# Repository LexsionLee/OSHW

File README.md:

# Lexsion 设计的开源硬件

> Open-source Hardware design from Lexsion

## 简介：

仓库名称取OSHW，顾名思义，本仓库存储 Lexsion 的开源硬件项目。因为贫穷导致无力购买高性能的新电脑以运行卡顿的Altium Designer ，外加近段时间其名声不好，笔者打算换一款EDA工具。听闻KiCad是一款开源的设计工具，于是笔者就选择了它。考虑开源硬件的特殊性，使用商业的EDA工具设计可能并不是一个好的选择，因此本项目下所有PCB设计，都是使用KiCad完成的。

每个项目相关内容存储在以项目名称命名的单独目录中。

### 项目目录内应该包含以下内容：

* Schematic design （KiCad 5.1x or KiCad 6(Future) ）
* PCB design （KiCad 5.1x or KiCad 6(Future) ）
* 自建 符号库 与 封装库 （KiCad 5.1x or KiCad 6(Future) ）
* PDF 打印的 Schematic （方便使用PDF Reader直接阅读）
* GERBER （方便直接发送给PCB制造商以进行制造）
* README.md （介绍项目内容、相关事项）

## 注意：

笔者本仓库下发布这些硬件设计的目的旨在研究和分享。这些设计视其所处的阶段可能没有被实际生产或大量测试过，因笔者技术水平所限，无法保证它们在实际使用中是否可以正常工作。因此 Lexsion 不对使用这些文件产生的损失或风险承担任何责任。这里不提供任何保障！(It's absolutely no WARRANTY.)

本仓库下的相关硬件设计有参考其他设计，笔者会避免将明确声明了禁止参考的内容应用于此处设计。如果此处的某些设计对您或您所在的组织构成侵权，您可以与我取得联系。

i[AT]lexsion.net，将[AT]换成@可邮件联系我。

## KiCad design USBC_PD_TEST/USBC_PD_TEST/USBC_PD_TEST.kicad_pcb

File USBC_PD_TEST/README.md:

# USBC_PD_TEST

此项目是一个用于USBC口下快速充电协议分析测试的转接板，采用四层板结构，确保能通过大电流。电源部分宽走线与接线柱设计，应该能轻易通过5A电流，测试环便于挂接逻辑分析仪。笔者主要用于学习PD规范过程中的实验验证，限于笔者才疏学浅，该测试板可能会有BUG，有问题欢迎反馈。

**注意：此项目暂未实际测试。**

## 效果图：

### 2D：

### 3D：

## 基本信息：

| 项目名称  | USBC_PD_TEST     |
| --------- | ---------------- |
| PCB工艺   | 0.8mm四层玻纤板  |
| PCB数量   | 1                |
| PCB尺寸   | 约49.5 * 40 (mm) |
| KiCad版本 | 6.0.4            |

## 其他事项：

该板要安装Type-C公头，板厚必须为0.8mm!

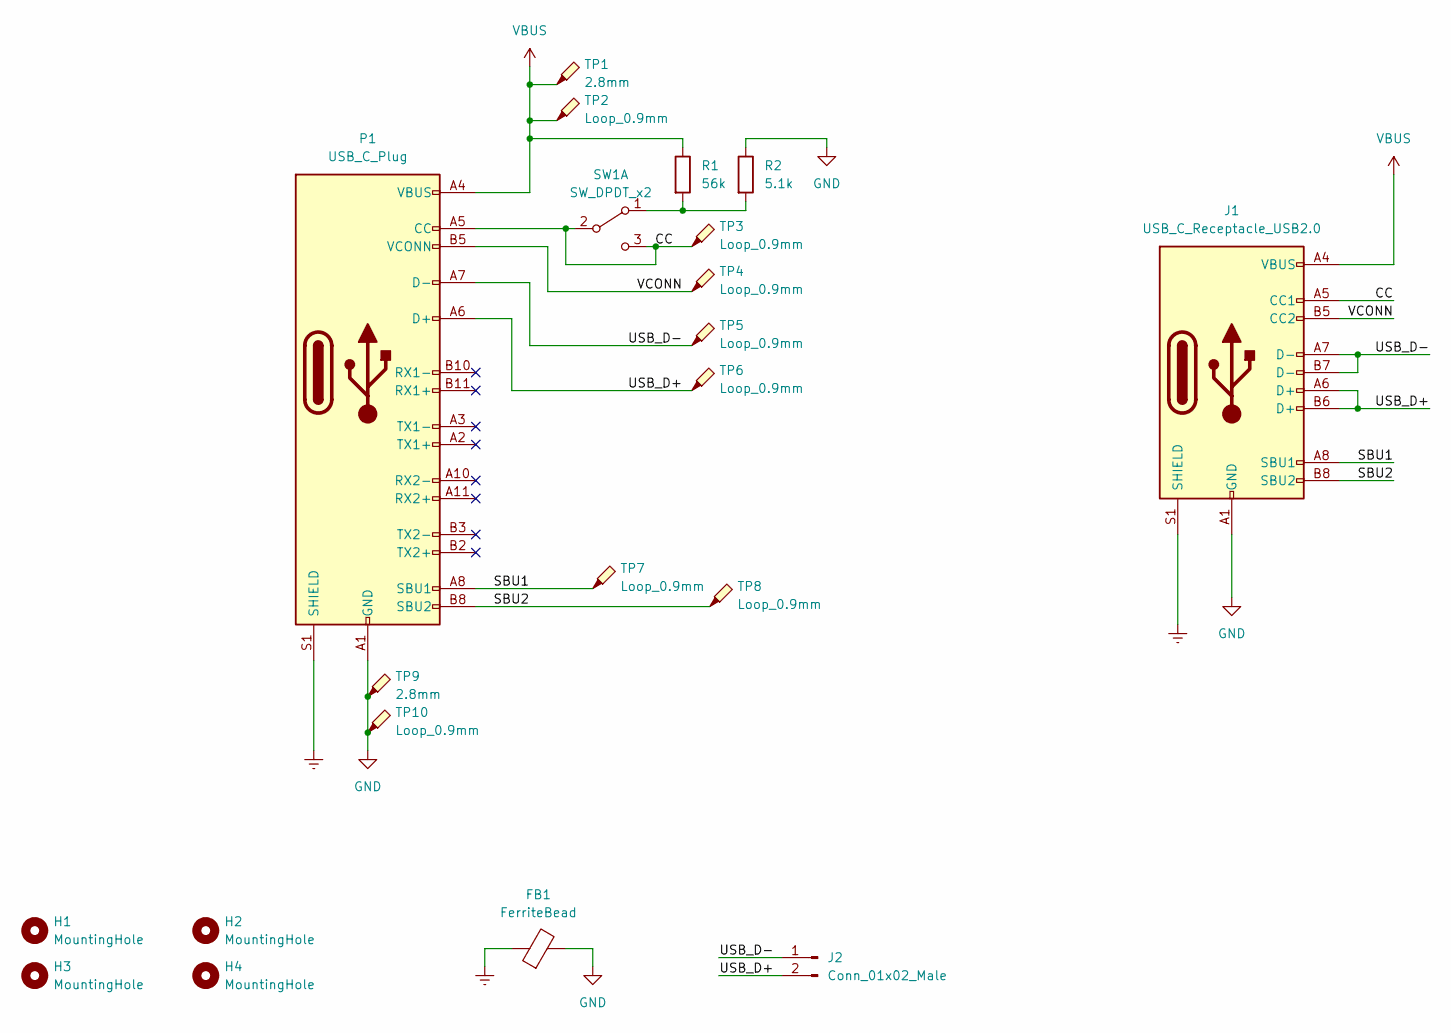
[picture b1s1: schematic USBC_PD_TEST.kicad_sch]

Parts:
FB1: FerriteBead; L_0603_1608Metric
H1, H2, H3, H4: MountingHole; MountingHole_3.2mm_M3_Pad_Via
J1: USB_C_Receptacle_USB2.0; USB_C_Receptacle_Palconn_UTC16-G
J2: Conn_01x02_Male; PinHeader_1x02_P2.54mm_Vertical
P1: USB_C_Plug; USB_C_Plug_Molex_105444
R1: 56k; R_0402_1005Metric
R2: 5.1k; R_0402_1005Metric
SW1: SW_DPDT_x2; SW_DPDT_MSS22D18
TP1, TP9: 2.8mm; TestPoint_Loop_D3.80mm_Drill2.8mm
TP2, TP3, TP4, TP5, TP6, TP7, TP8, TP10: Loop_0.9mm; TestPoint_Loop_D2.60mm_Drill0.9mm_Beaded

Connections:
/CC: J1.A5 (CC1), P1.A5 (CC), SW1.2 (B), SW1.3 (C), TP3.1
/SBU1: J1.A8 (SBU1), P1.A8 (SBU1), TP7.1
/SBU2: J1.B8 (SBU2), P1.B8 (SBU2), TP8.1
/USB_D+: J1.A6 (D+), J1.B6 (D+), J2.2, P1.A6 (D+), TP6.1
/USB_D-: J1.A7 (D-), J1.B7 (D-), J2.1, P1.A7 (D-), TP5.1
/VCONN: J1.B5 (CC2), P1.B5 (VCONN), TP4.1
Earth: FB1.1, J1.S1 (SHIELD), P1.S1 (SHIELD)
GND: FB1.2, J1.A1 (GND), J1.A12 (GND), J1.B1 (GND), J1.B12 (GND), P1.A1 (GND), P1.A12 (GND), P1.B1 (GND), P1.B12 (GND), R2.1, TP9.1, TP10.1
unnamed: R1.2, R2.2, SW1.1 (A)
VBUS: J1.A4 (VBUS), J1.A9 (VBUS), J1.B4 (VBUS), J1.B9 (VBUS), P1.A4 (VBUS), P1.A9 (VBUS), P1.B4 (VBUS), P1.B9 (VBUS), R1.1, TP1.1, TP2.1

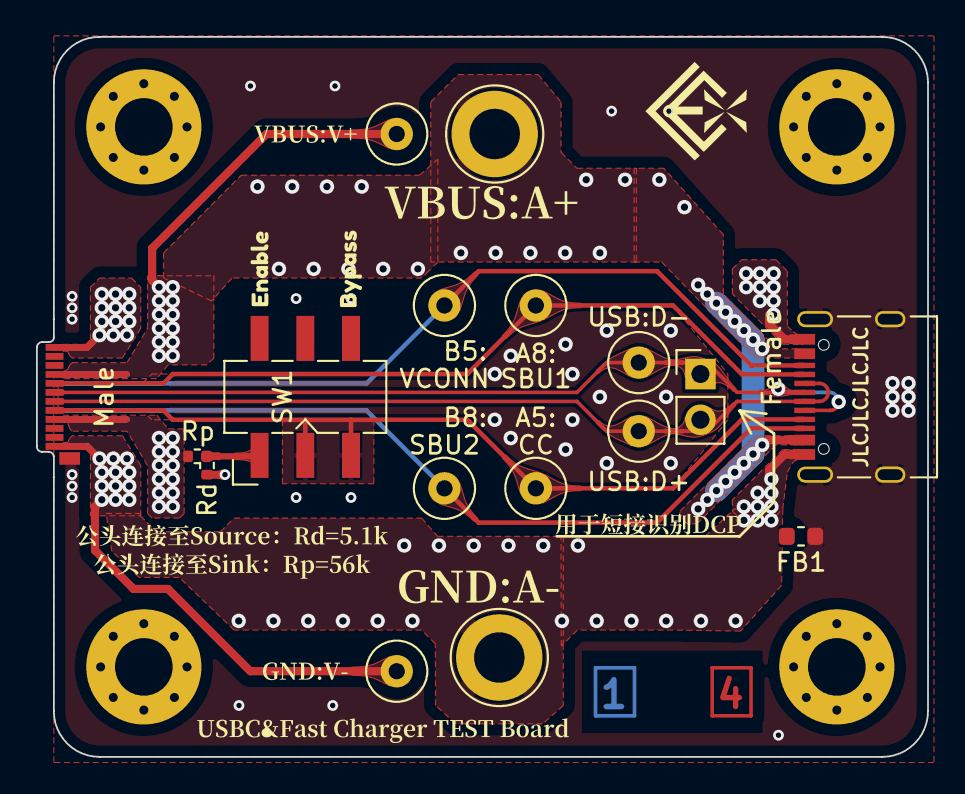
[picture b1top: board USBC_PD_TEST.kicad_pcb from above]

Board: 4 copper layers, 49.5 x 40.0 mm, 32 parts (1 on the bottom side), 10 nets.

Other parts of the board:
kibuzzard-6262F4E3: G***; kibuzzard-6262F4E3
kibuzzard-6262F4EB: G***; kibuzzard-6262F4EB
kibuzzard-6262F531: G***; kibuzzard-6262F531
kibuzzard-6262F952: G***; kibuzzard-6262F952
kibuzzard-6262FE0A: G***; kibuzzard-6262FE0A
kibuzzard-6262FE8D: G***; kibuzzard-6262FE8D
kibuzzard-6263C95A: G***; kibuzzard-6263C95A
kibuzzard-6263F752: G***; kibuzzard-6263F752
kibuzzard-62641BEE: G***; kibuzzard-62641BEE
kibuzzard-62641C40: G***; kibuzzard-62641C40
kibuzzard-62641778: G***; kibuzzard-62641778

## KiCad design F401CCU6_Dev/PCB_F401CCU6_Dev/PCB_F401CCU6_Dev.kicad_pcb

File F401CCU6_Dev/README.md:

# F401CCU6_Dev

此项目的目标是做一个引出所有IO，以实现一个F401CCU6开发板的效果。参考了网上常见的板型，加入了RGB灯。

该项目MCU采用的STM32F1401CCU6，偶然翻出几年前留下的几枚mPOS也是画这板子的原因之一。该板设计了RST、BOOT按键，并引出了SWD调试接口，同时为了迎合时代发展，USB采用了Type C接口。

## 效果图：

**实物图：**

**2D：**

**3D：**

## 基本信息：

| 项目名称  | F401CCU6_Dev   |
| --------- | -------------- |
| PCB工艺   | 双面玻纤板     |
| PCB数量   | 1              |
| PCB尺寸   | 约57 * 23 (mm) |
| KiCad版本 | 6.0.4          |

## 其他事项：

暂无。

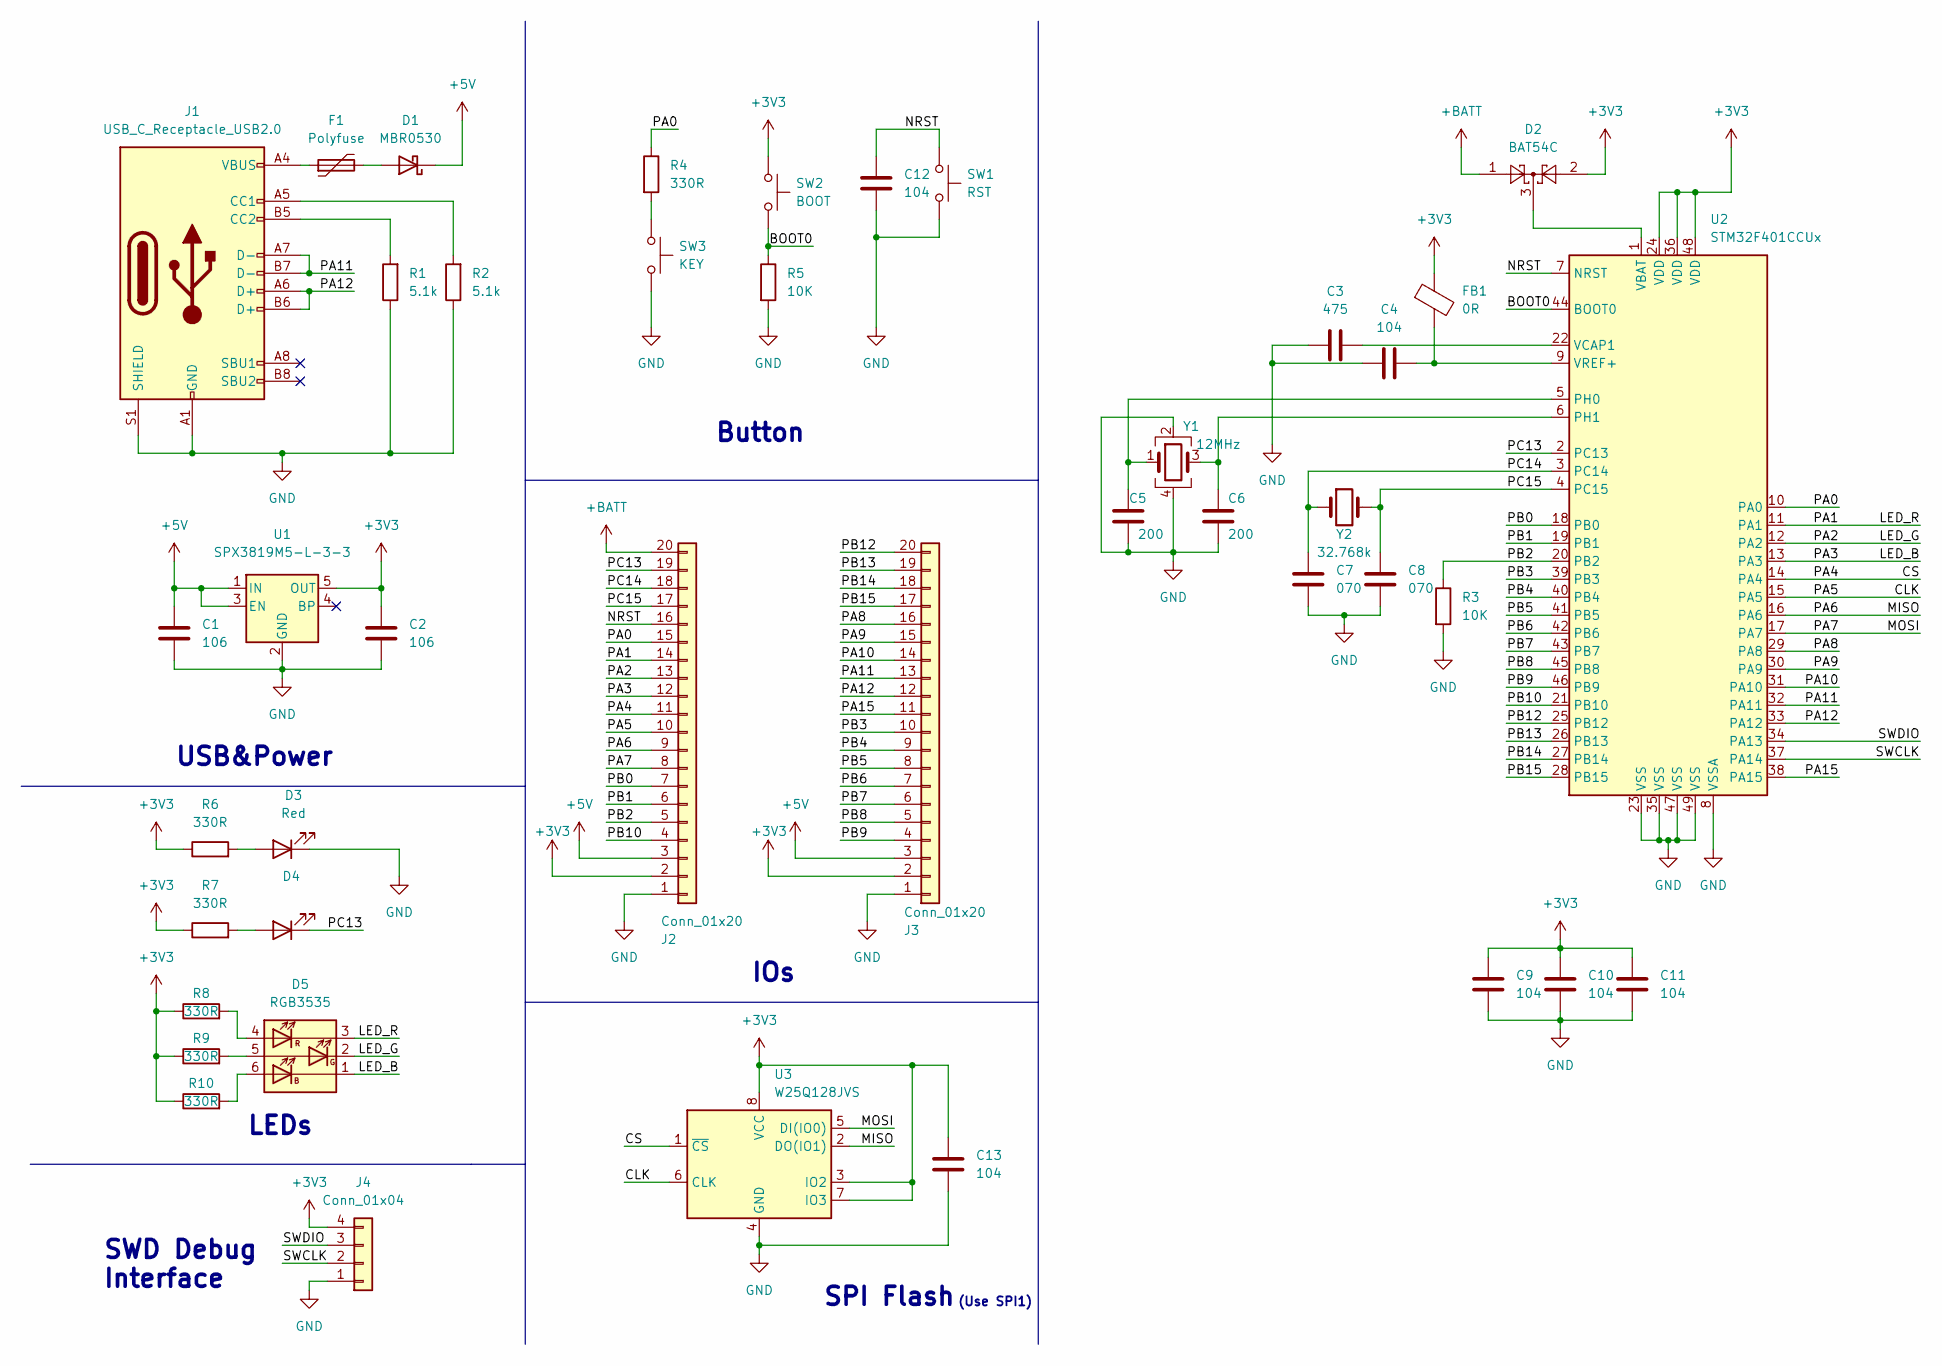
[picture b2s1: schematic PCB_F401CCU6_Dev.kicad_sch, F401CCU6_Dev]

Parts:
C1, C2: 106; C_0603_1608Metric
C3: 475; C_0402_1005Metric
C4, C9, C10, C11, C12, C13: 104; C_0402_1005Metric
C5, C6: 200; C_0402_1005Metric
C7, C8: 070; C_0402_1005Metric
D1: MBR0530; D_SOD-123
D2: BAT54C; SOT-23
D3: Red; LED_0603_1608Metric
D4: (no value)
D5: RGB3535; LED_RGB_3535
F1: Polyfuse; Fuse_0603_1608Metric
FB1: 0R; L_0603_1608Metric
J1: USB_C_Receptacle_USB2.0; USB_C_Receptacle_Palconn_UTC16-G
J2, J3: Conn_01x20; PinHeader_1x20_P2.54mm_Vertical
J4: Conn_01x04; PinHeader_1x04_P2.54mm_Horizontal
R1, R2: 5.1k; R_0402_1005Metric
R3, R5: 10K; R_0402_1005Metric
R4, R6, R7, R8, R9, R10: 330R; R_0402_1005Metric
SW1: RST; SW_Push_1P1T_TC026X
SW2: BOOT; SW_Push_1P1T_TC026X
SW3: KEY; SW_Push_1P1T_TC048X
U1: SPX3819M5-L-3-3; SOT-23-5
U2: STM32F401CCUx; QFN-48-1EP_7x7mm_P0.5mm_EP5.6x5.6mm
U3: W25Q128JVS; SOIC-8_5.23x5.23mm_P1.27mm
Y1: 12MHz; Crystal_SMD_3225-4Pin_3.2x2.5mm
Y2: 32.768k; Crystal_SMD_3215-2Pin_3.2x1.5mm

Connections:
+3V3: C2.1, C9.1, C10.1, C11.1, C13.1, D2.2, FB1.1, J2.2, J3.2, J4.4, R6.1, R7.1, R8.1, R9.1, R10.1, SW2.1, U1.5 (OUT), U2.24 (VDD), U2.36 (VDD), U2.48 (VDD), U3.3 (IO2), U3.7 (IO3), U3.8 (VCC)
+5V: C1.1, D1.1 (K), J2.3, J3.3, U1.1 (IN), U1.3 (EN)
+BATT: D2.1, J2.20
/BOOT0: R5.1, SW2.2, U2.44 (BOOT0)
/CLK: J2.10, U2.15 (PA5), U3.6 (CLK)
/CS: J2.11, U2.14 (PA4), U3.1 (~CS)
/LED_B: D5.1 (KB), J2.12, U2.13 (PA3)
/LED_G: D5.2 (KG), J2.13, U2.12 (PA2)
/LED_R: D5.3 (KR), J2.14, U2.11 (PA1)
/MISO: J2.9, U2.16 (PA6), U3.2 (DO(IO1))
/MOSI: J2.8, U2.17 (PA7), U3.5 (DI(IO0))
/NRST: C12.1, J2.16, SW1.1, U2.7 (NRST)
/PA0: J2.15, R4.1, U2.10 (PA0)
/PA8: J3.16, U2.29 (PA8)
/PA9: J3.15, U2.30 (PA9)
/PA10: J3.14, U2.31 (PA10)
/PA11: J1.A7 (D-), J1.B7 (D-), J3.13, U2.32 (PA11)
/PA12: J1.A6 (D+), J1.B6 (D+), J3.12, U2.33 (PA12)
/PA15: J3.11, U2.38 (PA15)
/PB0: J2.7, U2.18 (PB0)
/PB1: J2.6, U2.19 (PB1)
/PB2: J2.5, R3.1, U2.20 (PB2)
/PB3: J3.10, U2.39 (PB3)
/PB4: J3.9, U2.40 (PB4)
/PB5: J3.8, U2.41 (PB5)
/PB6: J3.7, U2.42 (PB6)
/PB7: J3.6, U2.43 (PB7)
/PB8: J3.5, U2.45 (PB8)
/PB9: J3.4, U2.46 (PB9)
/PB10: J2.4, U2.21 (PB10)
/PB12: J3.20, U2.25 (PB12)
/PB13: J3.19, U2.26 (PB13)
/PB14: J3.18, U2.27 (PB14)
/PB15: J3.17, U2.28 (PB15)
/PC13: D4.1 (K), J2.19, U2.2 (PC13)
/PC14: C7.1, J2.18, U2.3 (PC14), Y2.1
/PC15: C8.1, J2.17, U2.4 (PC15), Y2.2
/SWCLK: J4.2, U2.37 (PA14)
/SWDIO: J4.3, U2.34 (PA13)
GND: C1.2, C2.2, C3.1, C4.1, C5.2, C6.2, C7.2, C8.2, C9.2, C10.2, C11.2, C12.2, C13.2, D3.1 (K), J1.A1 (GND), J1.A12 (GND), J1.B1 (GND), J1.B12 (GND), J1.S1 (SHIELD), J2.1, J3.1, J4.1, R1.1, R2.1, R3.2, R5.2, SW1.2, SW3.2, U1.2 (GND), U2.8 (VSSA), U2.23 (VSS), U2.35 (VSS), U2.47 (VSS), U2.49 (VSS), U3.4 (GND), Y1.2, Y1.4
unnamed: C3.2, U2.22 (VCAP1)
unnamed: C4.2, FB1.2, U2.9 (VREF+)
unnamed: C5.1, U2.5 (PH0), Y1.1
unnamed: C6.1, U2.6 (PH1), Y1.3
unnamed: D1.2 (A), F1.2
unnamed: D2.3, U2.1 (VBAT)
unnamed: D3.2 (A), R6.2
unnamed: D4.2 (A), R7.2
unnamed: D5.4 (AR), R8.2
unnamed: D5.5 (AG), R9.2
unnamed: D5.6 (AB), R10.2
unnamed: F1.1, J1.A4 (VBUS), J1.A9 (VBUS), J1.B4 (VBUS), J1.B9 (VBUS)
unnamed: J1.A5 (CC1), R2.2
unnamed: J1.B5 (CC2), R1.2
unnamed: R4.2, SW3.1

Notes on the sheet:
(Use SPI1)
LEDs
Button
USB&Power
IOs
SPI Flash
SWD Debug Interface

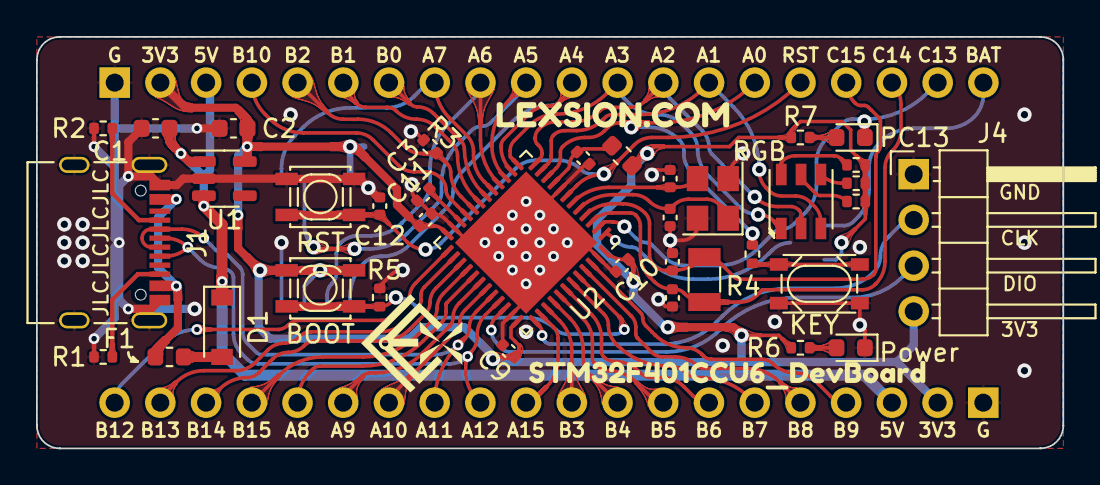
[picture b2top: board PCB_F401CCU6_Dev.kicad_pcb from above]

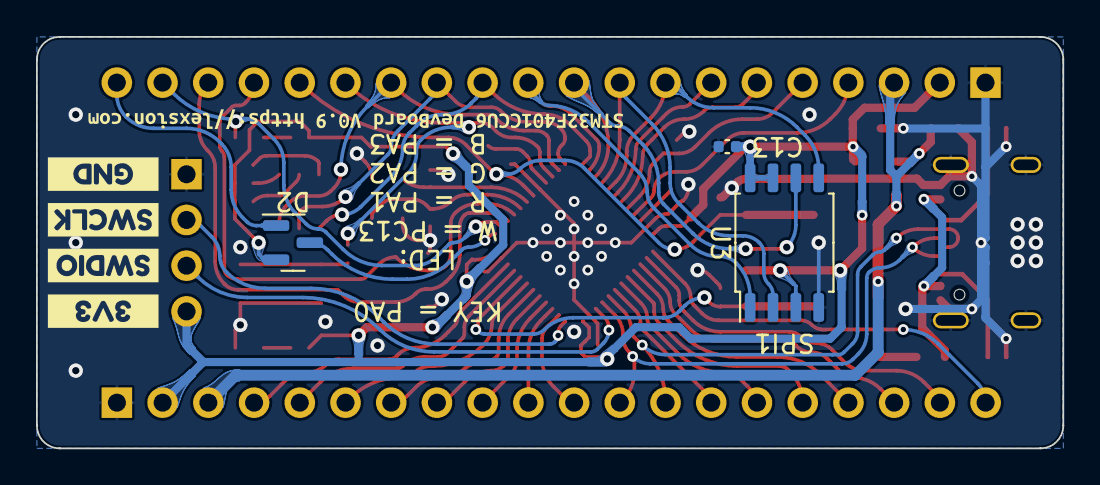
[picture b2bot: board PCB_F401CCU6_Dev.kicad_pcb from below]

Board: 2 copper layers, 57.0 x 22.9 mm, 50 parts (11 on the bottom side), 55 nets.

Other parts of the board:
kibuzzard-6240A2D2: G***; kibuzzard-6240A2D2
kibuzzard-6240A4EF: G***; kibuzzard-6240A4EF
kibuzzard-6240A22A: G***; kibuzzard-6240A22A
kibuzzard-6240A56D: G***; kibuzzard-6240A56D
kibuzzard-6240A129: G***; kibuzzard-6240A129
kibuzzard-6240A243: G***; kibuzzard-6240A243
kibuzzard-6240A270: G***; kibuzzard-6240A270
kibuzzard-62409F94: G***; kibuzzard-62409F94

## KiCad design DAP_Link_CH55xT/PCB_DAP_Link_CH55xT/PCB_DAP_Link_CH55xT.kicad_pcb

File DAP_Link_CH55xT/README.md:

# DAP_Link_CH55xT

此项目是一个 Type-C 接口的 DAP-Link。采用的CH554T方案，抄袭大佬[POSYSTORAGE的开源作品](https://github.com/posystorage/CH55x_HS_DAP-Link-v2)而来，原作使用的CH552G。大佬说对固件进行了优化，速度更快。本人手中只有几片CH554T，于是便画了这张板体验一番。

**警告：V0.9 丝印存在错误，正面的SW接口GND和RST针脚丝印标记放反了。正确丝印从上到下依次为Vtg、DIO、CLK、GND、RST ，此问题已在1.0版本中修正。功能测试可用，考虑配件成本，不再打样**

## 实物图：

## 效果图：

### 2D：

### 3D：

## 基本信息：

| 项目名称  | DAP_Link_CH55xT     |
| --------- | ------------------- |
| PCB工艺   | 1.6mm双面玻纤板     |
| PCB数量   | 1                   |
| PCB尺寸   | 约41.15 * 21.3 (mm) |
| KiCad版本 | 6.0.1               |

## 其他事项：

对比大佬开源的版本，我修改了总线收发器的取电为可选状态，可以通过短接上下部分在3.3V与5V电平间选择。如果不选，则需要通过Vtg连接目标系统电源取电。

PCB目前还没有实际验证，PCB没有预留额外编程器接口。

CH55x是通过出厂预置的USB Bootloader下载固件的，注意少了时不要损坏Bootloader，不要更改下载配置脚。

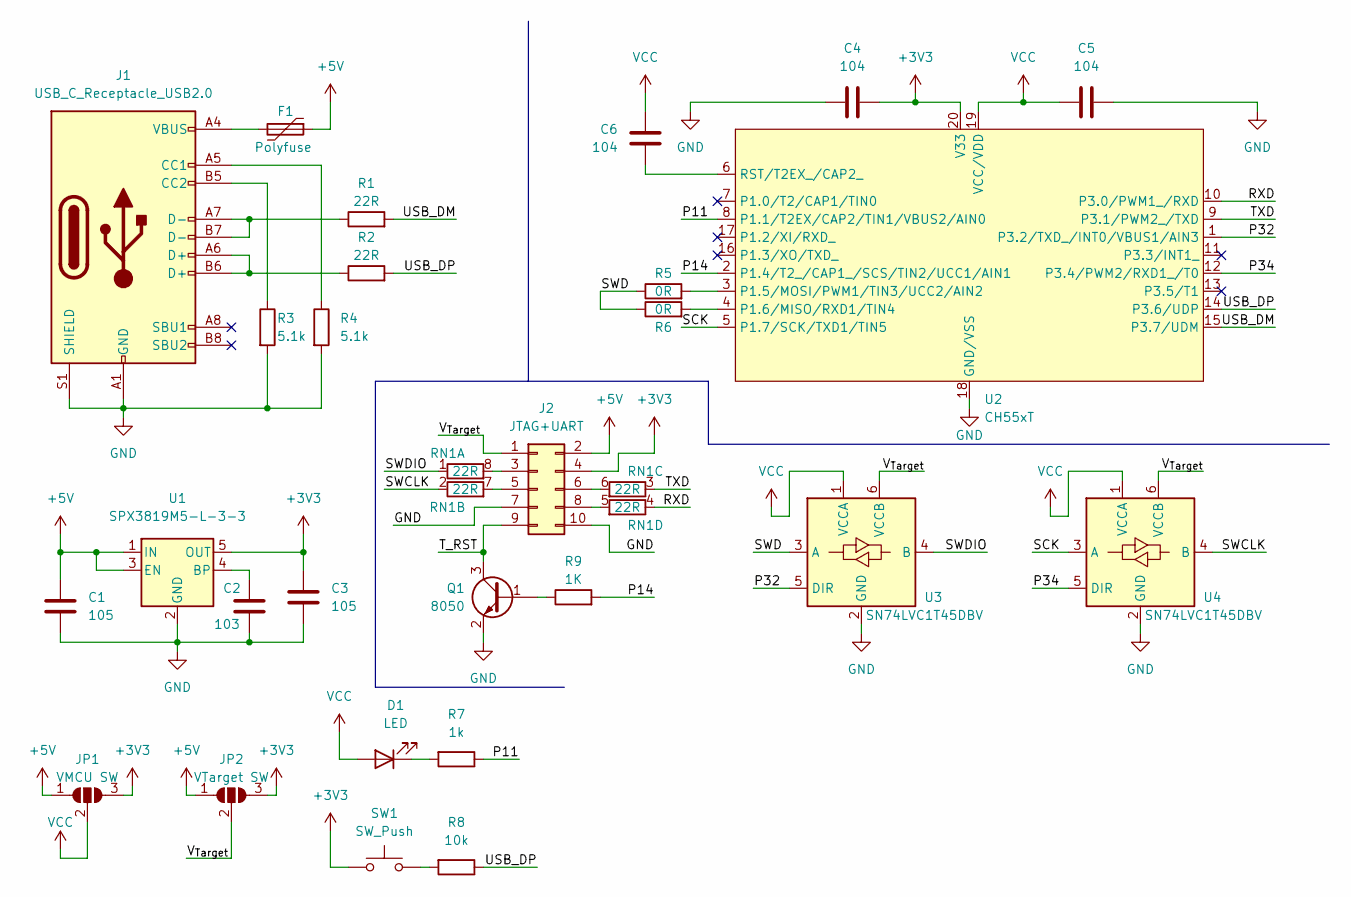
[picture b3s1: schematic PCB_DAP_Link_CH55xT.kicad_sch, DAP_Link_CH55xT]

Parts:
C1: 105; C_0805_2012Metric
C2: 103; C_0603_1608Metric
C3: 105; C_0603_1608Metric
C4, C5, C6: 104; C_0603_1608Metric
D1: LED; LED_0603_1608Metric
F1: Polyfuse; Fuse_0603_1608Metric
J1: USB_C_Receptacle_USB2.0; USB_C_Receptacle_Palconn_UTC16-G
J2: JTAG+UART; Link_JTAG_10Pin
JP1: VMCU SW; SolderJumper-3_P1.3mm_Open_RoundedPad1.0x1.5mm
JP2: VTarget SW; SolderJumper-3_P1.3mm_Open_RoundedPad1.0x1.5mm
Q1: 8050; SOT-23
R1, R2: 22R; R_0402_1005Metric
R3, R4: 5.1k; R_0603_1608Metric
R5, R6: 0R; R_0402_1005Metric
R7: 1k; R_0603_1608Metric
R8: 10k; R_0603_1608Metric
R9: 1K; R_0603_1608Metric
RN1: 22R; R_Array_Convex_4x0603
SW1: SW_Push; SW_Push_SPST_NO_Alps_SKRK
U1: SPX3819M5-L-3-3; SOT-23-5
U2: CH55xT; SSOP-20_4.4x6.5mm_P0.65mm
U3, U4: SN74LVC1T45DBV; SOT-23-6

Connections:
+3V3: C3.1, C4.2, J2.4, JP1.3 (B), JP2.3 (B), SW1.1, U1.5 (OUT), U2.20 (V33)
+5V: C1.1, F1.1, J2.2, JP1.1 (A), JP2.1 (A), U1.1 (IN), U1.3 (EN)
/P11: R7.1, U2.8 (P1.1/T2EX/CAP2/TIN1/VBUS2/AIN0)
/P14: R9.2, U2.2 (P1.4/T2_/CAP1_/SCS/TIN2/UCC1/AIN1)
/P32: U2.1 (P3.2/TXD_/INT0/VBUS1/AIN3), U3.5 (DIR)
/P34: U2.12 (P3.4/PWM2/RXD1_/T0), U4.5 (DIR)
/RXD: RN1.4 (R4.1), U2.10 (P3.0/PWM1_/RXD)
/SCK: U2.5 (P1.7/SCK/TXD1/TIN5), U4.3 (A)
/SWCLK: RN1.2 (R2.1), U4.4 (B)
/SWD: R5.1, R6.1, U3.3 (A)
/SWDIO: RN1.1 (R1.1), U3.4 (B)
/TXD: RN1.3 (R3.1), U2.9 (P3.1/PWM2_/TXD)
/T_RST: J2.9, Q1.3 (C)
/USB_DM: R1.2, U2.15 (P3.7/UDM)
/USB_DP: R2.2, R8.1, U2.14 (P3.6/UDP)
/V_{Target}: J2.1, JP2.2 (C), U3.6 (VCCB), U4.6 (VCCB)
GND: C1.2, C2.2, C3.2, C4.1, C5.2, J1.A1 (GND), J1.A12 (GND), J1.B1 (GND), J1.B12 (GND), J1.S1 (SHIELD), J2.7, J2.10, Q1.2 (E), R3.2, R4.2, U1.2 (GND), U2.18 (GND/VSS), U3.2 (GND), U4.2 (GND)
unnamed: C2.1, U1.4 (BP)
unnamed: C6.1, U2.6 (RST/T2EX_/CAP2_)
unnamed: D1.1 (K), R7.2
unnamed: F1.2, J1.A4 (VBUS), J1.A9 (VBUS), J1.B4 (VBUS), J1.B9 (VBUS)
unnamed: J1.A5 (CC1), R4.1
unnamed: J1.A6 (D+), J1.B6 (D+), R2.1
unnamed: J1.A7 (D-), J1.B7 (D-), R1.1
unnamed: J1.B5 (CC2), R3.1
unnamed: J2.3, RN1.8 (R1.2)
unnamed: J2.5, RN1.7 (R2.2)
unnamed: J2.6, RN1.6 (R3.2)
unnamed: J2.8, RN1.5 (R4.2)
unnamed: Q1.1 (B), R9.1
unnamed: R5.2, U2.3 (P1.5/MOSI/PWM1/TIN3/UCC2/AIN2)
unnamed: R6.2, U2.4 (P1.6/MISO/RXD1/TIN4)
unnamed: R8.2, SW1.2
VCC: C5.1, C6.2, D1.2 (A), JP1.2 (C), U2.19 (VCC/VDD), U3.1 (VCCA), U4.1 (VCCA)

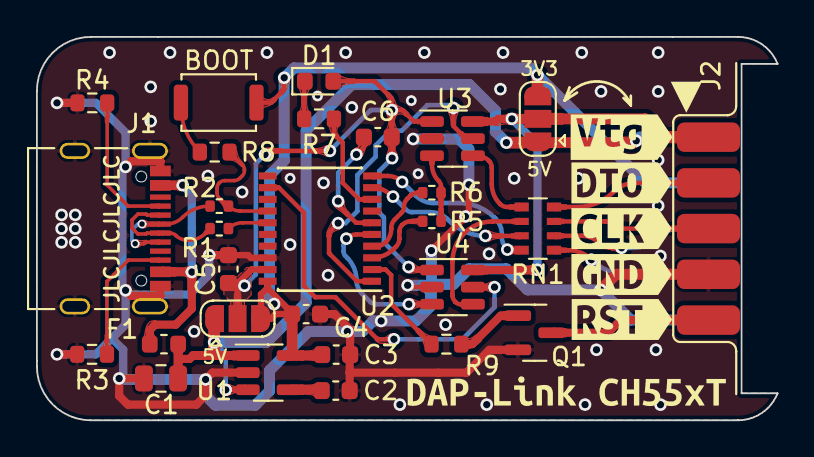
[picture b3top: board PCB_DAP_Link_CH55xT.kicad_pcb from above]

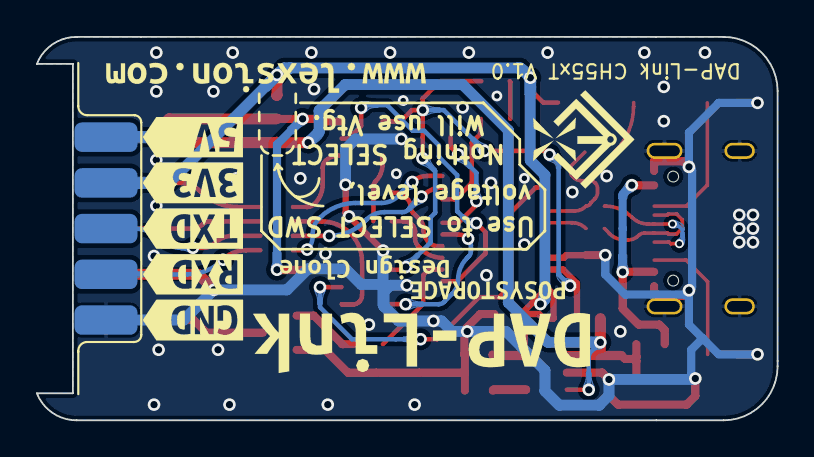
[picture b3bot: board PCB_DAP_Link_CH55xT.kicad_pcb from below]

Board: 2 copper layers, 41.1 x 21.3 mm, 43 parts (9 on the bottom side), 34 nets.

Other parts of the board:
kibuzzard-620E0A42: G***; kibuzzard-620E0A42
kibuzzard-620E0A67: G***; kibuzzard-620E0A67
kibuzzard-620E0A89: G***; kibuzzard-620E0A89
kibuzzard-620E0A96: G***; kibuzzard-620E0A96
kibuzzard-620E0B10: G***; kibuzzard-620E0B10
kibuzzard-620E0C5F: G***; kibuzzard-620E0C5F
kibuzzard-620E0C39: G***; kibuzzard-620E0C39
kibuzzard-620E0C75: G***; kibuzzard-620E0C75
kibuzzard-620E0C82: G***; kibuzzard-620E0C82
kibuzzard-620E6B95: G***; kibuzzard-620E6B95
kibuzzard-620E6DC2: G***; kibuzzard-620E6DC2
kibuzzard-620E09F5: G***; kibuzzard-620E09F5
kibuzzard-620E78D0: G***; kibuzzard-620E78D0
kibuzzard-620E7650: G***; kibuzzard-620E7650
kibuzzard-620E7763: G***; kibuzzard-620E7763

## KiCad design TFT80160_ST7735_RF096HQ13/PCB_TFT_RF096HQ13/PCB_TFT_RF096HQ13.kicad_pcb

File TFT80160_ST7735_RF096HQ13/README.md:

# TFT80160_ST7735_RF096HQ13

此项目是一个 80\*RGB\*160 的 TFT 模块。采用的SPI接口竖向TFT，据说多种款式，FPC丝印大概是96HQ13，13Pin 0.7mm间距FPC直接焊接，猜测控制器为ST7735S。屏幕隔壁老王处购得，本人还未到货，据说碎屏率较高，翻车。屏幕对外的8Pin接口，采用的是业界常用的开发板屏幕接口线序。

尺寸为0.96" 的13Pin SPI TFT 很常见，看大家都是同样的脚位。

注意：此项目暂未实际测试。

## 效果图：

### 2D：

### 3D：

## 基本信息：

| 项目名称  | TFT80160_ST7735_RF096HQ13 |
| --------- | ------------------------- |
| PCB工艺   | 1.2mm双面玻纤板           |
| PCB数量   | 1                         |
| PCB尺寸   | 约35 * 30 (mm)            |
| KiCad版本 | 6.0.1                     |

## 其他事项：

装配时需要使用双面胶将屏幕贴在顶层，然后将排线折至底层焊接，焊接方式建议可使用烙铁拖焊。

ST7735驱动代码可在网上搜索解决。有些知名开发板公司已经提供了常见平台的Demo.

其他可参考ST7735S的文档。

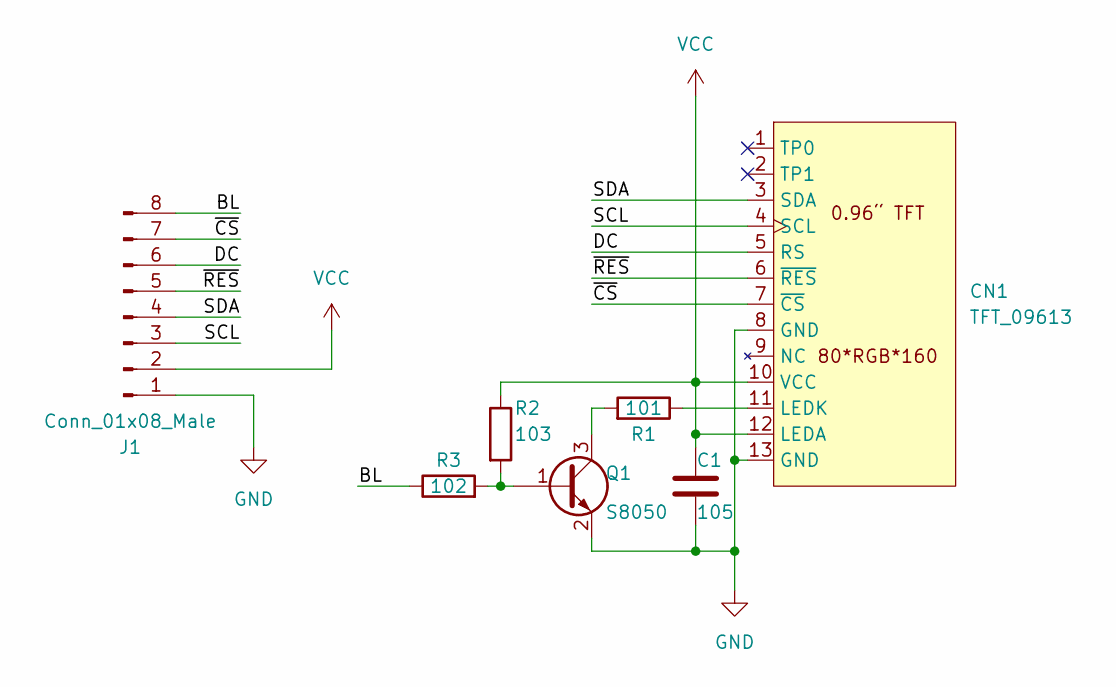
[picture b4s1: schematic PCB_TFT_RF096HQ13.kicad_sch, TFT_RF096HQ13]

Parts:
C1: 105; C_0603_1608Metric
CN1: TFT_09613; LCM_Solder_13Pin_0.7mm
J1: Conn_01x08_Male; PinHeader_1x08_P2.54mm_Vertical
Q1: S8050; SOT-23
R1: 101; R_1206_3216Metric
R2: 103; R_0603_1608Metric
R3: 102; R_0603_1608Metric

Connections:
/BL: J1.8, R3.1
/DC: CN1.5 (RS), J1.6
/SCL: CN1.4 (SCL), J1.3
/SDA: CN1.3 (SDA), J1.4
/~CS: CN1.7 (~CS), J1.7
/~RES: CN1.6 (~RES), J1.5
GND: C1.2, CN1.8 (GND), CN1.13 (GND), J1.1, Q1.2 (E)
unnamed: CN1.11 (LEDK), R1.1
unnamed: Q1.1 (B), R2.2, R3.2
unnamed: Q1.3 (C), R1.2
VCC: C1.1, CN1.10 (VCC), CN1.12 (LEDA), J1.2, R2.1

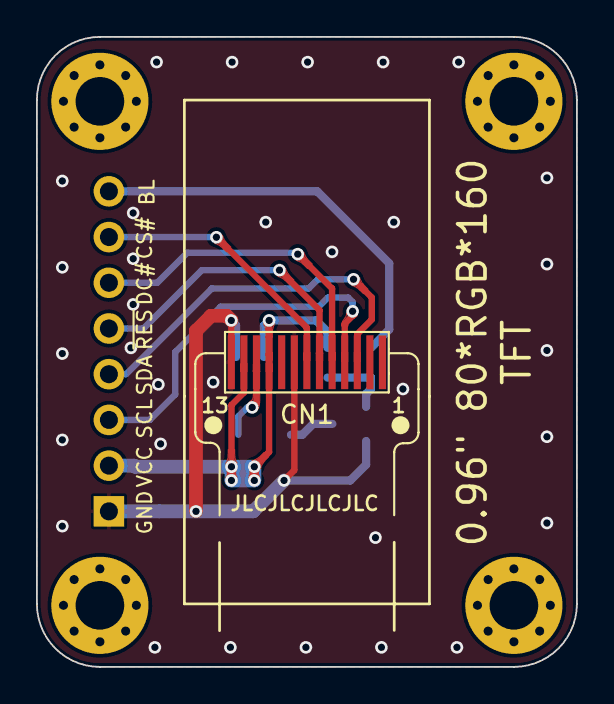
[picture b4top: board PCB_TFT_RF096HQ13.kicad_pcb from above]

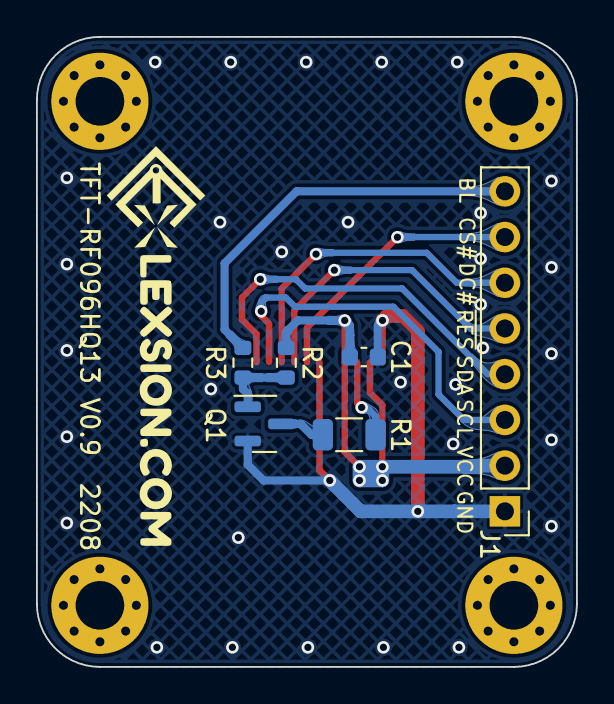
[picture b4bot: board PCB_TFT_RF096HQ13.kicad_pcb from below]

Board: 2 copper layers, 30.0 x 35.0 mm, 8 parts (7 on the bottom side), 11 nets.

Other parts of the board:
kibuzzard-6211093F: G***; kibuzzard-6211093F

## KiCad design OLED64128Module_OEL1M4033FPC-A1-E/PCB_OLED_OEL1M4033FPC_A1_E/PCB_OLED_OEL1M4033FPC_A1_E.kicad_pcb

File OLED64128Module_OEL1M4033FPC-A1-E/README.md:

# OLED64128Module_OEL1M4033FPC-A1-E

此项目是一个64128OLED模块。采用的竖向OLED，FPC丝印为OEL1M4033FPC-A1-E，22Pin 0.7mm间距FPC直接焊接，控制器为SH1107。屏幕隔壁老王处购得，据说坏屏占比达70%，大翻车。屏幕对外的8Pin接口，采用的是业界常用的开发板屏幕接口线序，只用到了其中七个针脚。

万能的群友提供了几个22Pin接口的定义图，最终确定屏幕的22Pin接口定义如下：

## 效果图：

### 实物图：

### 2D：

### 3D：

## 基本信息：

| 项目名称  | OLED64128Module_OEL1M4033FPC-A1-E |
| --------- | --------------------------------- |
| PCB工艺   | 1.2mm双面玻纤板                   |
| PCB数量   | 1                                 |
| PCB尺寸   | 约40 * 29 (mm)                    |
| KiCad版本 | 6.0.1                             |

## TODO：

1. - [ ] I2C与SPI选择跳线添加电阻，以防错误配置导致短路？

## 其他事项：

装配时需要使用双面胶将屏幕贴在顶层，然后将排线折至底层焊接，焊接方式建议可使用烙铁拖焊。

驱动代码可在网上搜索解决。OLED驱动IC型号为SH1107，有些知名开发板公司已经提供了常见平台的Demo。拨动开关与旁边的跳点功能一致，使用时二选一，用途是切换4线SPI模式和I2C模式。**注意：跳线点只能选择短接一端，若同时短接会导致3V3对GND短路！**

选择SPI模式时I2C的两个上拉电阻可以不焊。OLED的IM0没有引出，无法设置为3线SPI。

其他可参考SH1107文档。

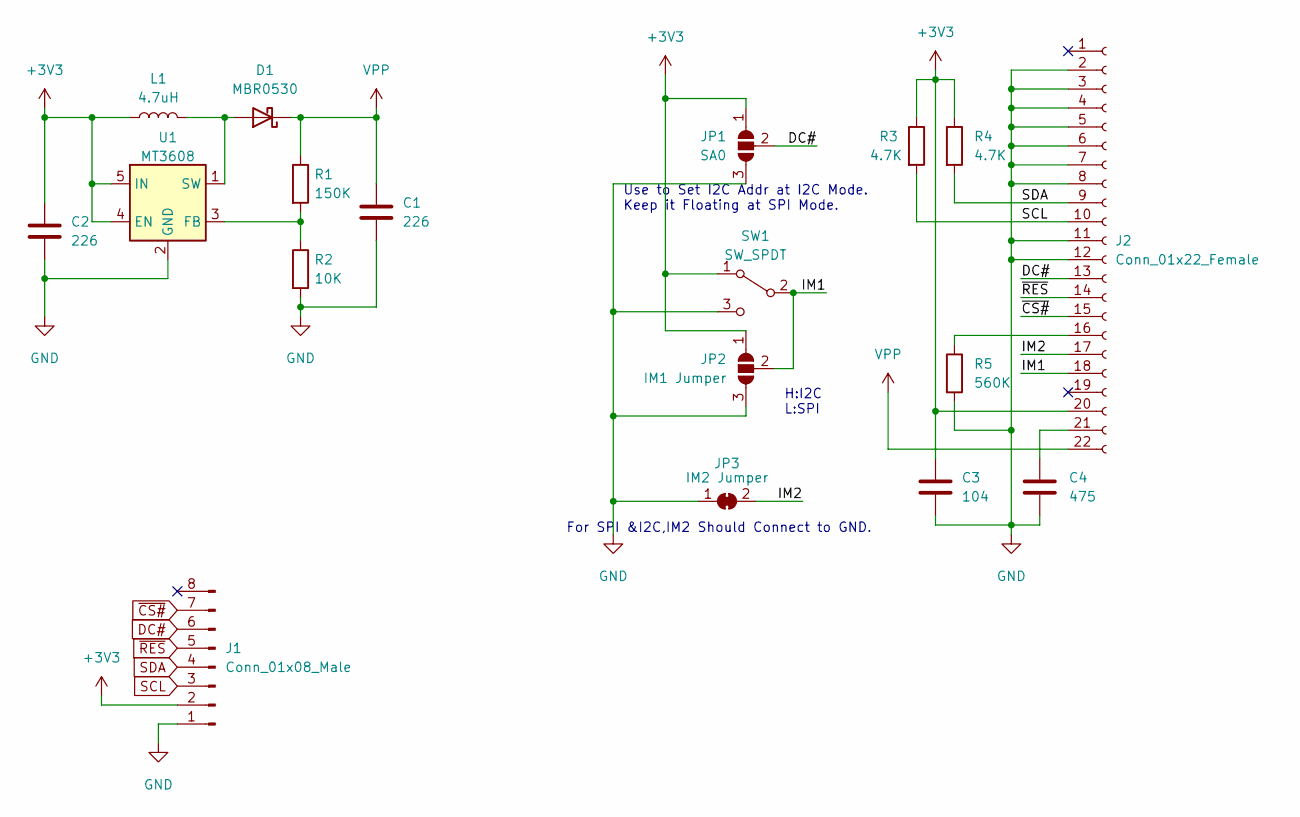
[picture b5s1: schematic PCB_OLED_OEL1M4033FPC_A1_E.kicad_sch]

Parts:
C1: 226; C_0805_2012Metric
C2: 226; C_0603_1608Metric
C3: 104; C_0603_1608Metric
C4: 475; C_0805_2012Metric
D1: MBR0530; D_SOD-123
J1: Conn_01x08_Male; PinHeader_1x08_P2.54mm_Vertical
J2: Conn_01x22_Female; LCM_Solder_22Pin_0.7mm
JP1: SA0; SolderJumper-3_P1.3mm_Open_Pad1.0x1.5mm
JP2: IM1 Jumper; SolderJumper-3_P2.0mm_Open_TrianglePad1.0x1.5mm
JP3: IM2 Jumper; SolderJumper-2_P1.3mm_Bridged_Pad1.0x1.5mm
L1: 4.7uH; L_1008_2520Metric
R1: 150K; R_0603_1608Metric
R2: 10K; R_0603_1608Metric
R3, R4: 4.7K; R_0603_1608Metric
R5: 560K; R_0603_1608Metric
SW1: SW_SPDT; SW_SPDT_PCM12
U1: MT3608; SOT-23-6

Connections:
+3V3: C2.1, C3.1, J1.2, J2.20, JP1.1 (A), JP2.1 (A), L1.1, R3.1, R4.1, SW1.1 (A), U1.4 (EN), U1.5 (IN), U1.6 (NC)
/IM1: J2.18, JP2.2 (C), SW1.2 (B)
/IM2: J2.17, JP3.2 (B)
DC#: J1.6, J2.13, JP1.2 (C)
GND: C1.2, C2.2, C3.2, C4.2, J1.1, J2.2, J2.3, J2.4, J2.5, J2.6, J2.7, J2.8, J2.11, J2.12, JP1.3 (B), JP2.3 (B), JP3.1 (A), R2.2, R5.2, SW1.3 (C), U1.2 (GND)
unnamed: C4.1, J2.21
unnamed: D1.2 (A), L1.2, U1.1 (SW)
unnamed: J2.16, R5.1
unnamed: R1.2, R2.1, U1.3 (FB)
SCL: J1.3, J2.10, R3.2
SDA: J1.4, J2.9, R4.2
VPP: C1.1, D1.1 (K), J2.22, R1.1
~CS#: J1.7, J2.15
~RES: J1.5, J2.14

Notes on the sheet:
H:I2C L:SPI
Use to Set I2C Addr at I2C Mode. Keep it Floating at SPI Mode.
For SPI &I2C,IM2 Should Connect to GND.

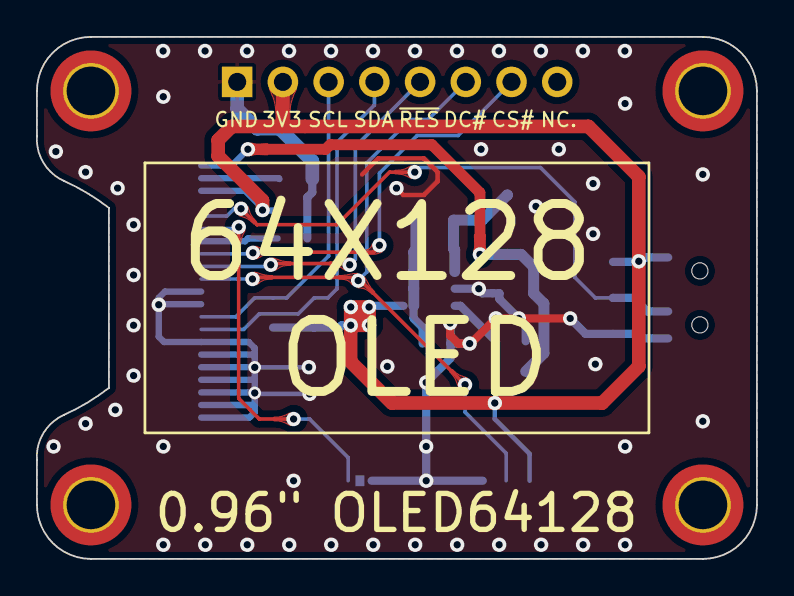
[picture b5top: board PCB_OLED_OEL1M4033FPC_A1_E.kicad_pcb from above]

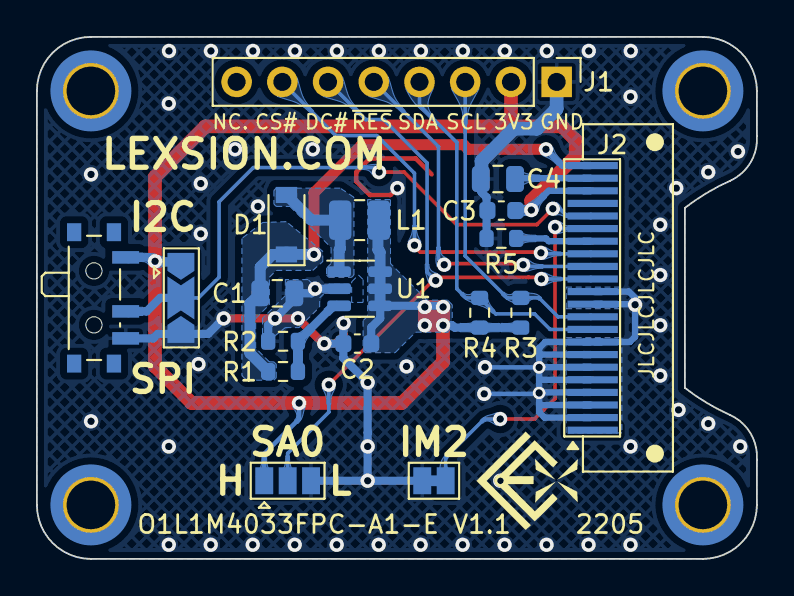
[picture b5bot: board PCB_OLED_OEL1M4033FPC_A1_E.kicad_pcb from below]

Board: 2 copper layers, 40.0 x 29.0 mm, 18 parts (18 on the bottom side), 14 nets.
